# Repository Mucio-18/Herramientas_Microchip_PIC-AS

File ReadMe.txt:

Este repositorio contiene diferentes carpetas con bibliotecas 
PCBs y footprints para microcontroladores PIC 
Bibliotecas en lenguaje c y ensamblador,
utilizando el compilador XC8 pic-as de Microchip.

A continuación encontrarás carpetas como:
-PCBs
	Contienen esquematicos, PCBs y archivos de 
	manufactura para tarjetas de desarrollo con
	microcontroladores PIC al igual que huellas
	universales para diferentes encapsulados
	8, 14, 18, 20, 28 y 40 pines DIP
-Plantillas:
	Contienen plantillas para crear códigos de ensamblador
	de manera más rapida y correctamente estructurada, 
	cada código está organizado en carpetas de acuerdo
	a la familia de microcontroladores PIC, por ejemplo
	la familia mid range con los PIC16FXXX.
	En cada carpeta encontrarás un archivo main.S
-Bibliotecas:
	Contiene bibliotecas para usar en códigos de c/ensamblador,
	facilitando la implementación o control de ciertos 
	periféricos u operaciones complejas del lenguaje, 
	las bibliotecas están separadas por familias
	de microcontroladores, como la familia mid range para
	PIC16FXXX.
	En cada carpeta encontrarás un archivo .inc

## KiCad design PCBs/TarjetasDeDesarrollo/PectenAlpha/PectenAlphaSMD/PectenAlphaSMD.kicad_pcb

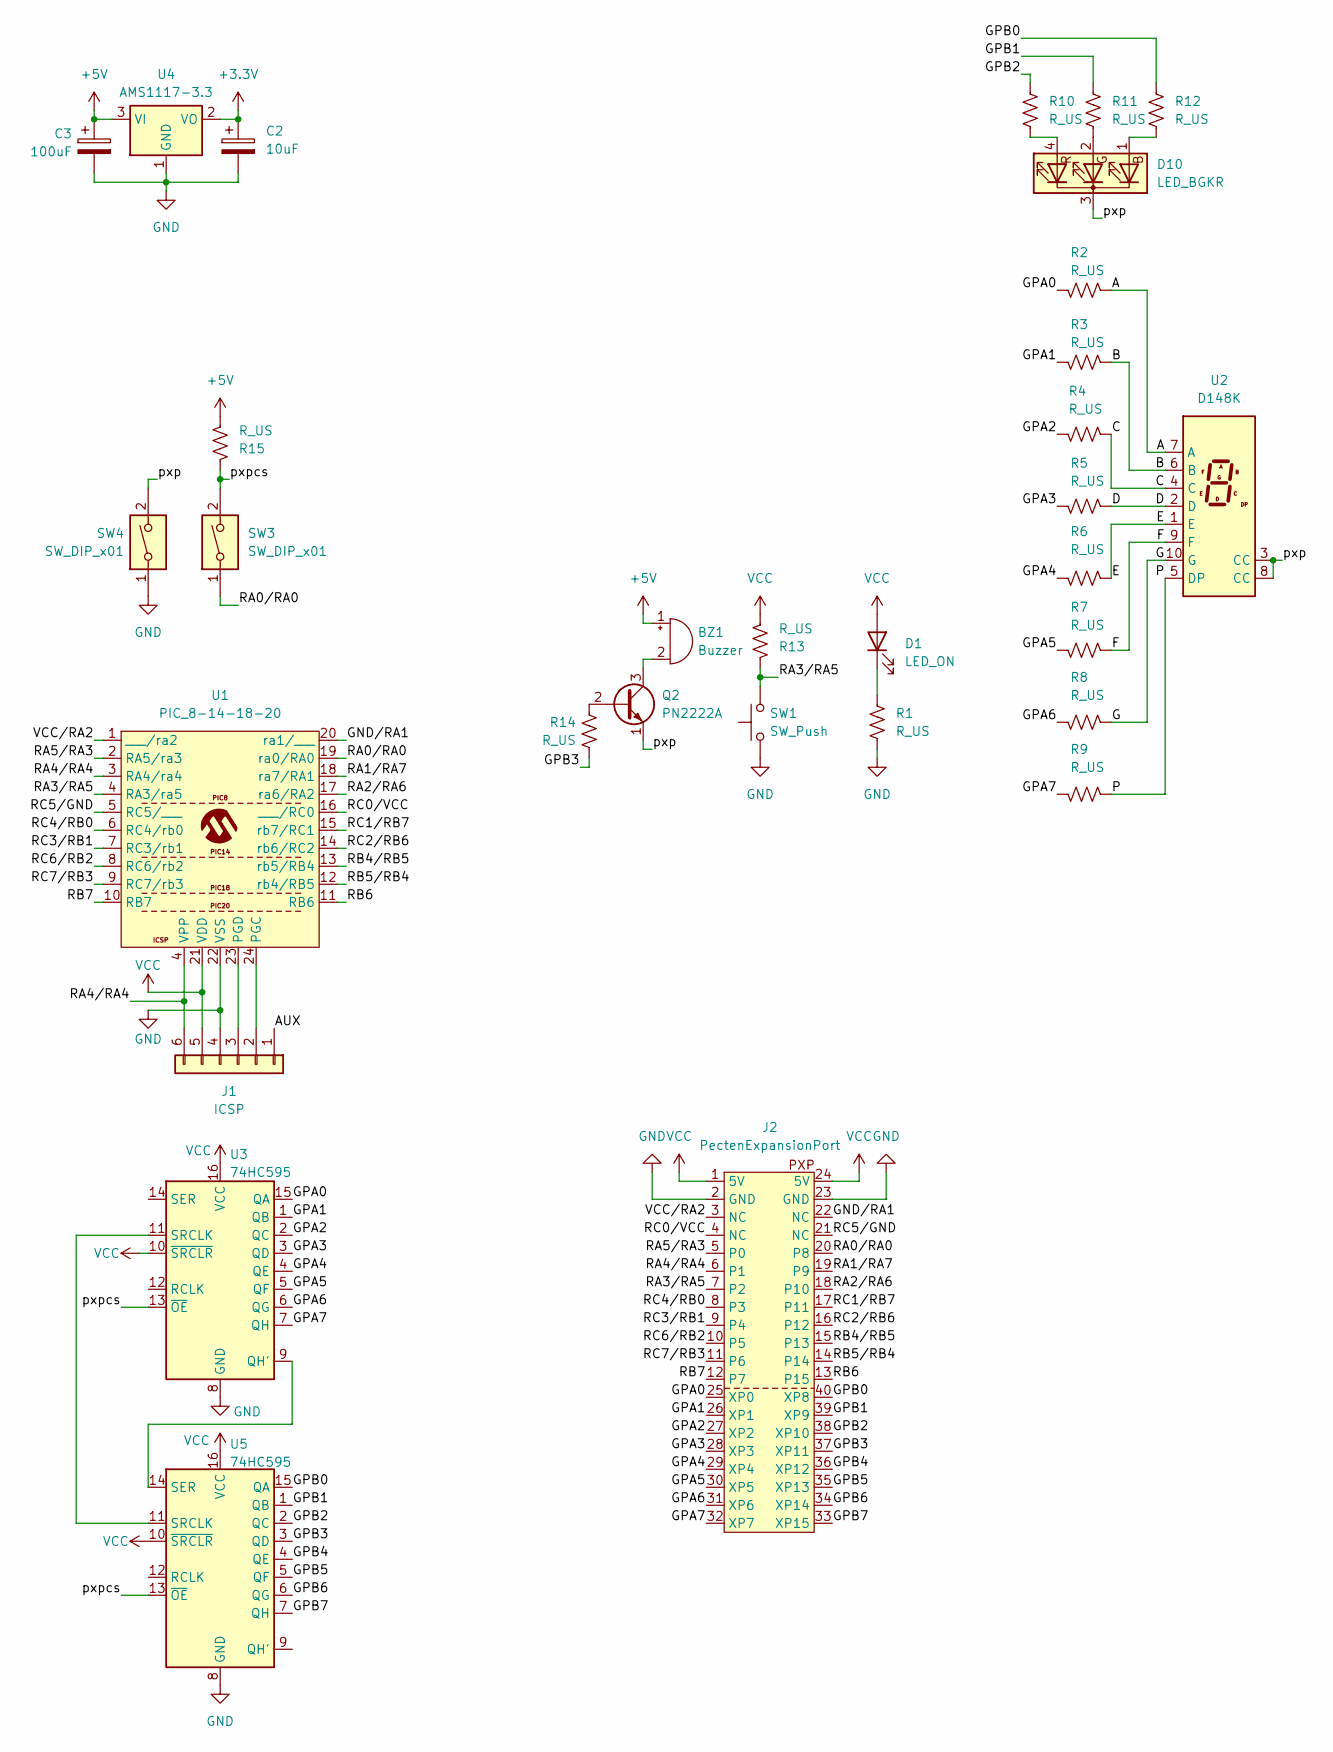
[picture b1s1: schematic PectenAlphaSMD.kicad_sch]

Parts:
BZ1: Buzzer; Buzzer_12x9.5RM7.6
C2: 10uF; CP_Elec_5x3
C3: 100uF; CP_Elec_5x3
D1: LED_ON; LED_1206_3216Metric
D10: LED_BGKR; LED_RGB_5050-6
J1: ICSP; PinHeader_1x06_P2.54mm_Horizontal
J2: PectenExpansionPort; PXP
Q2: PN2222A; TO-92_Inline
R1, R2, R3, R4, R5, R6, R7, R8, R9, R10, R11, R12, R13, R14, R15: R_US; R_0805_2012Metric_Pad1.20x1.40mm_HandSolder
SW1: SW_Push; SW_PUSH_6mm_H4.3mm
SW3, SW4: SW_DIP_x01; SW_DIP_SPSTx01_Slide_6.7x4.1mm_W7.62mm_P2.54mm_LowProfile
U1: PIC_8-14-18-20
U2: D148K; D1X8K
U3, U5: 74HC595; SOP-16_4.4x10.4mm_P1.27mm
U4: AMS1117-3.3; SOT-223-3_TabPin2

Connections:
+3.3V: C2.1, U4.2 (VO)
+5V: BZ1.1 (+), C3.1, R15.2, U4.3 (VI)
/A: R2.2, U2.7 (A)
/AUX: J1.1
/B: R3.2, U2.6 (B)
/C: R4.2, U2.4 (C)
/D: R5.2, U2.2 (D)
/E: R6.2, U2.1 (E)
/F: R7.2, U2.9 (F)
/G: R8.2, U2.10 (G)
/GND/RA1: J2.22 (NC), U1.20 (ra1/___)
/GPA0: J2.25 (XP0), R2.1, U3.15 (QA)
/GPA1: J2.26 (XP1), R3.1, U3.1 (QB)
/GPA2: J2.27 (XP2), R4.1, U3.2 (QC)
/GPA3: J2.28 (XP3), R5.1, U3.3 (QD)
/GPA4: J2.29 (XP4), R6.1, U3.4 (QE)
/GPA5: J2.30 (XP5), R7.1, U3.5 (QF)
/GPA6: J2.31 (XP6), R8.1, U3.6 (QG)
/GPA7: J2.32 (XP7), R9.1, U3.7 (QH)
/GPB0: J2.40 (XP8), R12.1, U5.15 (QA)
/GPB1: J2.39 (XP9), R11.1, U5.1 (QB)
/GPB2: J2.38 (XP10), R10.1, U5.2 (QC)
/GPB3: J2.37 (XP11), R14.2, U5.3 (QD)
/GPB4: J2.36 (XP12), U5.4 (QE)
/GPB5: J2.35 (XP13), U5.5 (QF)
/GPB6: J2.34 (XP14), U5.6 (QG)
/GPB7: J2.33 (XP15), U5.7 (QH)
/P: R9.2, U2.5 (DP)
/RA0/RA0: J2.20 (P8), SW3.1, U1.19 (ra0/RA0)
/RA1/RA7: J2.19 (P9), U1.18 (ra7/RA1)
/RA2/RA6: J2.18 (P10), U1.17 (ra6/RA2)
/RA5/RA3: J2.5 (P0), U1.2 (RA5/ra3)
/RB4/RB5: J2.15 (P13), U1.13 (rb5/RB4)
/RB5/RB4: J2.14, U1.12 (rb4/RB5)
/RB6: J2.13 (P15), U1.11 (RB6)
/RB7: J2.12 (P7), U1.10 (RB7)
/RC0/VCC: J2.4 (NC), U1.16 (___/RC0)
/RC1/RB7: J2.17 (P11), U1.15 (rb7/RC1)
/RC2/RB6: J2.16 (P12), U1.14 (rb6/RC2)
/RC3/RB1: J2.9 (P4), U1.7 (RC3/rb1)
/RC4/RB0: J2.8 (P3), U1.6 (RC4/rb0)
/RC5/GND: J2.21 (NC), U1.5 (RC5/___)
/RC6/RB2: J2.10 (P5), U1.8 (RC6/rb2)
/RC7/RB3: J2.11 (P6), U1.9 (RC7/rb3)
/VCC/RA2: J2.3 (NC), U1.1 (___/ra2)
/pxp: D10.3 (K), Q2.1 (E), SW4.2, U2.3 (CC), U2.8 (CC)
/pxpcs: R15.1, SW3.2, U3.13 (~OE), U5.13 (~OE)
GND: C2.2, C3.2, J1.4, J2.2 (GND), J2.23 (GND), R1.2, SW1.1, SW4.1, U1.22 (VSS), U3.8 (GND), U4.1 (GND), U5.8 (GND)
unnamed: BZ1.2 (-), Q2.3 (C)
unnamed: D1.1 (K), R1.1
unnamed: D10.1 (BA), R12.2
unnamed: D10.2 (GA), R11.2
unnamed: D10.4 (RA), R10.2
unnamed: J1.2, U1.24 (PGC)
unnamed: J1.3, U1.23 (PGD)
unnamed: Q2.2 (B), R14.1
unnamed: U3.9 (QH'), U5.14 (SER)
VCC: D1.2 (A), J1.5, J2.1 (5V), J2.24 (5V), R13.2, U1.21 (VDD), U3.10 (~SRCLR), U3.16 (VCC), U5.10 (~SRCLR), U5.16 (VCC)

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
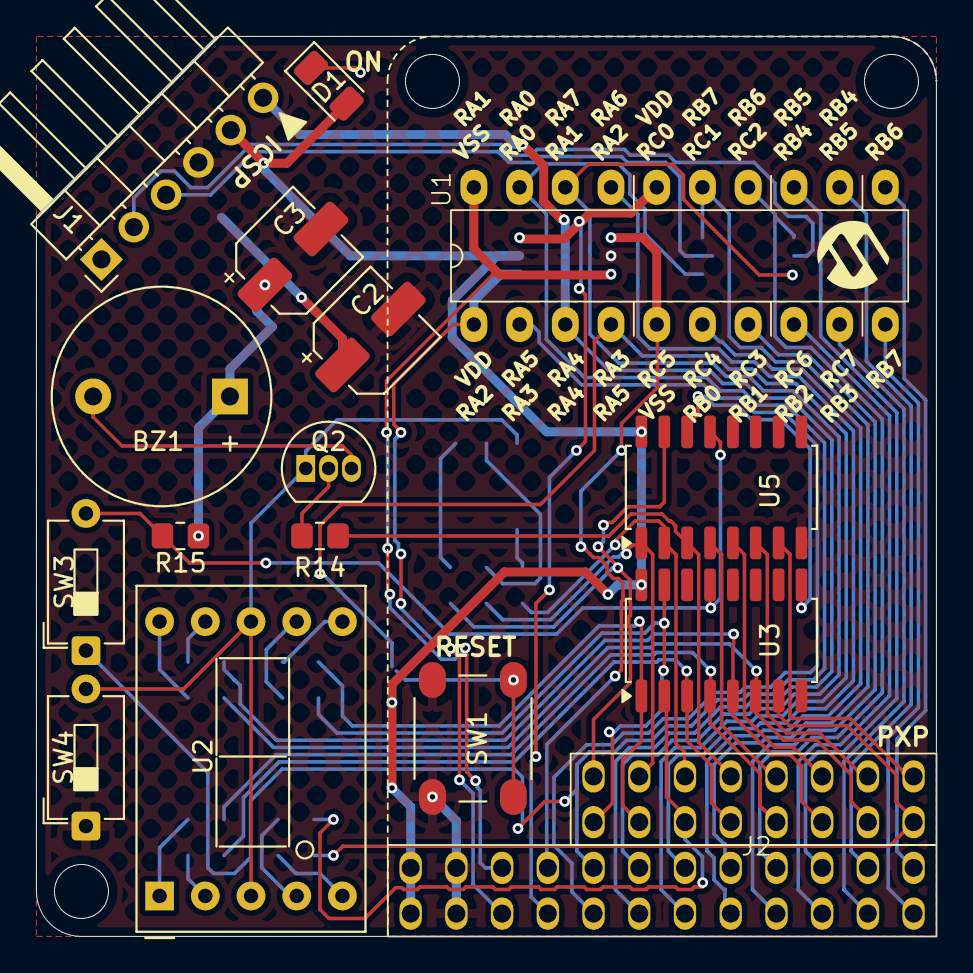
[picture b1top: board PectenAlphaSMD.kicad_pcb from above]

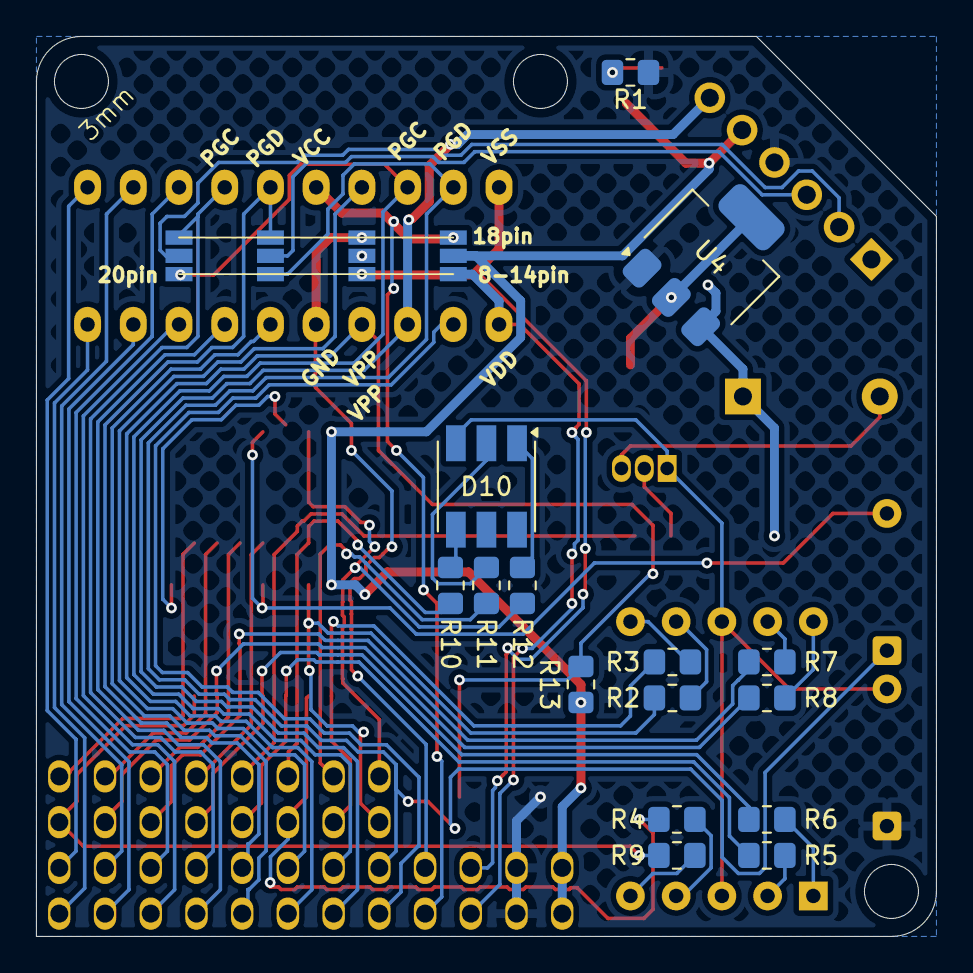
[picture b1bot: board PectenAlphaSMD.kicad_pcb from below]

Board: 2 copper layers, 50.0 x 50.0 mm, 31 parts (15 on the bottom side), 59 nets.

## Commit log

2025-11-05 Se creó una nueva biblioteca SPI usando macros, falta probar si el compilador los detecta correctamente
2025-11-05 Correcciones de sintaxis de SPI_software.inc
2025-11-06 Se crearon delays para 4MHz y 8MHz en midrange
2025-11-06 Se eliminó la licencia GNU
2025-11-06 Se creó un nuevo experimento de biblioteca SPI con macros, sigue en depuracion
2025-11-14 Creacion de una biblioteca universal multi oscilador (no terminada)
2025-11-18 avance de la biblioteca cronos
2025-12-16 Se crearon las primeras huellas universales de PICs dip
2025-12-17 se agregaron los simbolos de las PCBs de 8-20 pines
2025-12-18 Se agregaron simbolos y paquetes de 28-40 pines
2025-12-18 Se corrigió el pin MCLR del pic de 18 pines y se comenzó el esquemático de la tarjeta pecten alpha
2026-01-17 Se modificaron las bibliotecas de delays para hacerlas más dinámicas aún en desarrollo
2026-01-18 Se terminó la biblioteca de retardos para 4MHz
2026-01-18 Se terminó biblioteca delay para 4, 8 y 10MHz
2026-01-18 Se agregaron 16 y 20MHz en retardos, biblioteca delays terminada
2026-01-19 Se agregó una biblioteca de conversión binario a BCD (readme.txt aún pendiente)
2026-01-20 Se terminó el archivo readme.txt de bin2bcd
2026-01-20 se modificó la plantilla midrange para que sea mas facil de entender
2026-02-27 Se crearon bibliotecas spi por software "bit bang"
2026-03-01 Se actualizó la biblioteca de la pecten Alpha pero se harán modificaciones para el CH340 usb a ttl
2026-03-01 Se tiene la PCB preliminar con forma de pecten alpha
2026-03-03 Se inició una importante modificación de la tarjeta pectenAlpha
2026-06-30 Modificacion a PectenAplhaSMD
